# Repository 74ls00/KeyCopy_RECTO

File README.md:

### Простой копировщик домофонных ключей от RECTO.

#### Портативный одноплатный SMD вариант с батарейным питанием.
[Подробнее в Wiki](https://github.com/74ls00/KeyCopy_RECTO/wiki).

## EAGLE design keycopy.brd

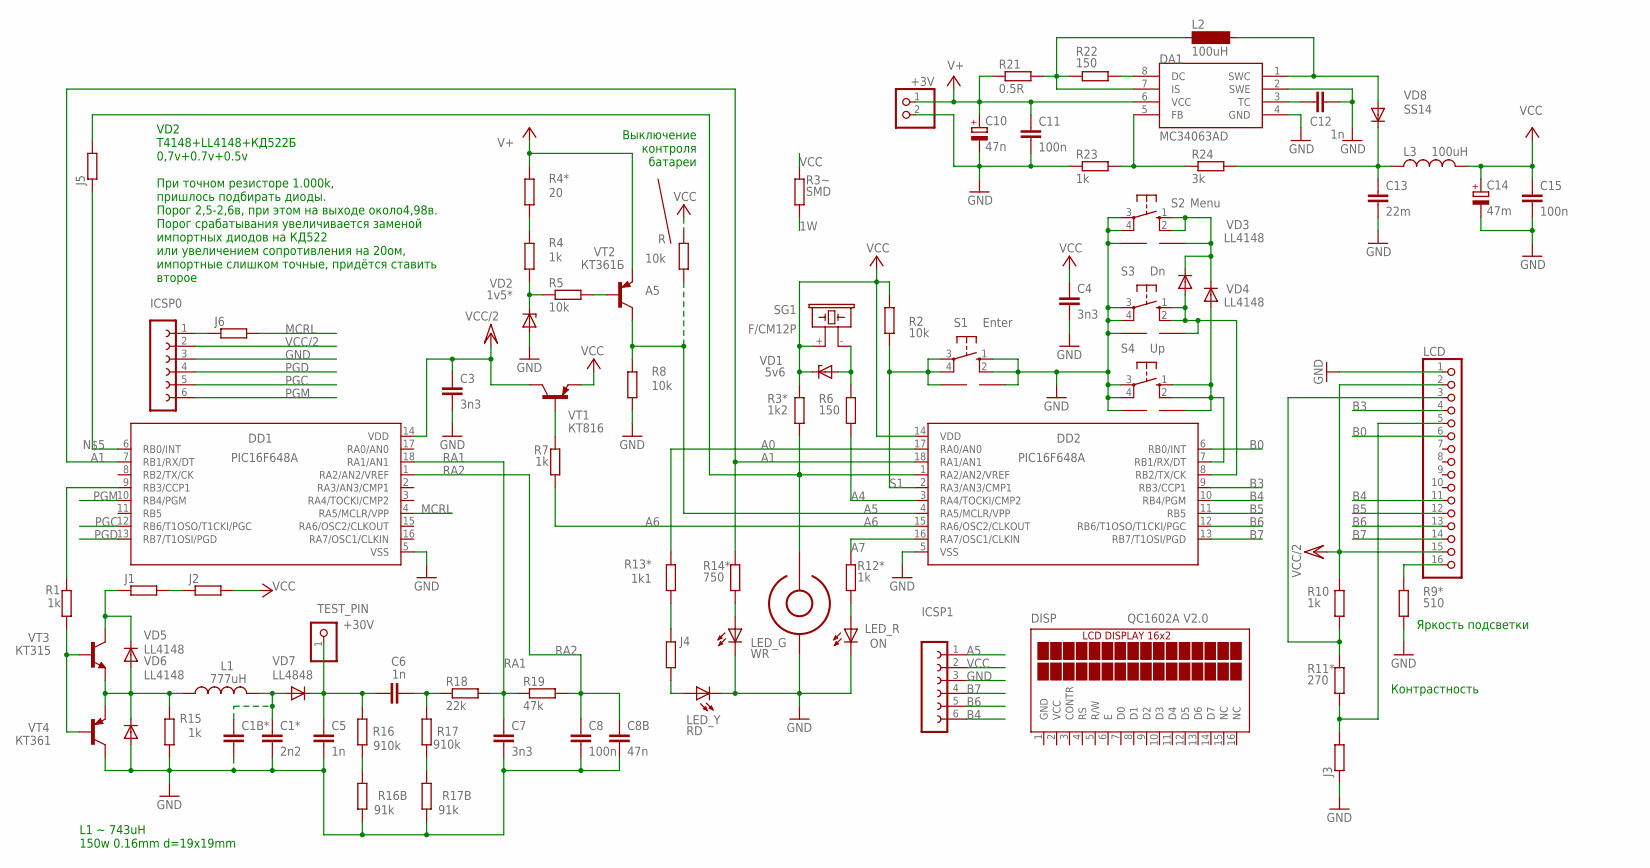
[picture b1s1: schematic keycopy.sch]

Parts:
+3V: PINHD-1X2; 1X02
C1*: 2n2; C025-030X050
C1B*: C-EU025-030X050; C025-030X050
C3, C4: 3n3; CAP-PTH-LARGE
C5, C6: 1n; C025-030X050
C7: 3n3; C025-030X050
C8: 100n; C025-030X050
C8B: 47n; C025-030X050
C10: 47n; E2,5-6
C11, C15: 100n; C0805K
C12: 1n; C0805K
C13: 22m; C1210
C14: 47m; E2,5-6
DA1: MC34063AD; SOIC8
DD1: PIC16F648A; SO-18W; MPN PIC16F628-20I/SO
DD2: PIC16F648A; SO-18W
DISP: QC1602A V2.0; TUXGR_16X2_1
ICSP0, ICSP1: FE06-1; FE06
J1, J2, J3, J4, J5: R-EU_R1206W; R1206W
J6: R-EU_R0805W; R0805W
KEY: DS1990
L1: 777uH; 0207/2V
L2: 100uH; SD12K100
L3: 100uH; 0207/12
LCD: PINHD-1X16; 1X16
LED_G: WR; LED3MM
LED_R: ON; LED3MM
LED_Y: RD; LED3MM
R, R5: 10k; R0805
R1, R4: 1k; R1206W
R2, R8: 10k; R1206W
R3*: 1k2; 0204/7
R3~: SMD; M0805
R4*: 20; R0805
R6, R22: 150; R0805
R7, R10, R12*, R15, R23: 1k; R0805
R9*: 510; R0805
R11*: 270; 0207/10
R13*: 1k1; 0207/10
R14*: 750; 0207/10
R16, R17: 910k; R0805
R16B, R17B: 91k; R0805
R18: 22k; R0805
R19: 47k; R0805
R21: 0.5R; R0805
R24: 3k; R1206W
S1: Enter; B3F-10XX
S2: Menu; B3F-10XX
S3: Dn; B3F-10XX
S4: Up; B3F-10XX
SG1: F/CM12P
TEST_PIN: +30V; 1X01
U$1, U$6, U$7, U$8: PROGRAMMER_5.08; PROGRAMMER_KEY
VD1: 5v6; SOD80C
VD2: 1v5*; ZDIO-5
VD3, VD4, VD5, VD6: LL4148; SOD80C
VD7: LL4848; SOD80C
VD8: SS14; SMB
VT1: КТ816; TO126
VT2: КТ361Б; TO92-BCE
VT3: КТ315; TO92-ECB
VT4: КТ361; TO92-BCE

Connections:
1W: DD2.1 (RA2/AN2/VREF), J5.2, KEY.P$1, R3*.1, R3~.1
A0: DD2.17 (RA0/AN0), R13*.2
A1: DD1.7 (RB1/RX/DT), DD2.18 (RA1/AN1), R14*.2
A4: DD2.3 (RA4/TOCKI/CMP2), R6.1
A5: DD2.4 (RA5/MCLR/VPP), ICSP1.1, R.1, R8.2, VT2.C
A6: DD2.15 (RA6/OSC2/CLKOUT), R7.1
A7: DD2.16 (RA7/OSC1/CLKIN), R12*.2
B0: DD2.6 (RB0/INT), LCD.6
B3: DD2.9 (RB3/CCP1), LCD.4
B4: DD2.10 (RB4/PGM), ICSP1.6, LCD.11
B5: DD2.11 (RB5), LCD.12
B6: DD2.12 (RB6/T1OSO/T1CKI/PGC), ICSP1.5, LCD.13
B7: DD2.13 (RB7/T1OSI/PGD), ICSP1.4, LCD.14
GND: +3V.2, C1*.2, C1B*.2, C3.2, C4.2, C5.2, C7.2, C8.2, C8B.2, C10.-, C11.2, C12.2, C13.2, C14.-, C15.2, DA1.2 (SWE), DA1.4 (GND), DD1.5 (VSS), DD2.5 (VSS), DISP.1 (GND), ICSP0.3, ICSP1.3, J3.1, KEY.P$2, LCD.1, LED_G.K (C), LED_R.K (C), LED_Y.K (C), R8.1, R9*.1, R15.1, R16B.1, R17B.1, R23.1, S1.1 (S), S1.2 (S1), S2.3, S2.4 (P1), S3.3, S3.4 (P1), S4.3, S4.4 (P1), U$1.P$2, U$6.P$1, U$7.P$1, U$8.P$1, VD2.A, VD6.A, VT4.C
LG: LED_G.A, R14*.1
LR: LED_R.A, R12*.1
LY: J4.1, LED_Y.A
MCRL: DD1.4 (RA5/MCLR/VPP), J6.2
unnamed: R1.1, VT3.B, VT4.B
unnamed: C1*.1, C1B*.1, L1.2, VD7.A
unnamed: C13.1, L3.1, R24.2, VD8.C
unnamed: DD1.9 (RB3/CCP1), R1.2
unnamed: DD1.6 (RB0/INT), J5.1
unnamed: C5.1, C6.1, R16.2, TEST_PIN.1, VD7.C
unnamed: R7.2, VT1.3 (B)
unnamed: R6.2, SG1.- (2), VD1.A
unnamed: LCD.16, R9*.2
unnamed: J1.1, VD5.C, VT3.C
unnamed: R16.1, R16B.2
unnamed: LCD.3, R10.1, R11*.2
unnamed: DD2.7 (RB1/RX/DT), S4.1 (S), S4.2 (S1), U$6.P$2, VD4.A
unnamed: S2.1 (S), S2.2 (S1), U$8.P$2, VD3.C, VD4.C
unnamed: DD2.8 (RB2/TX/CK), S3.1 (S), S3.2 (S1), U$7.P$2, VD3.A
unnamed: C6.2, R17.2, R18.1
unnamed: R4.1, R5.1, VD2.C
unnamed: R5.2, VT2.B
unnamed: ICSP0.1, J6.1
unnamed: J4.2, R13*.1
unnamed: L1.1, R15.2, VD5.A, VD6.C, VT3.E, VT4.E
unnamed: J1.2, J2.1
unnamed: R17.1, R17B.2
unnamed: J3.2, LCD.5, R11*.1
unnamed: C12.1, DA1.3 (TC)
unnamed: DA1.1 (SWC), L2.2, VD8.A
unnamed: DA1.7 (IS), L2.1, R21.2, R22.1
unnamed: DA1.8 (DC), R22.2
unnamed: DA1.5 (FB), R23.2, R24.1
unnamed: R4.2, R4*.1
PGC: DD1.12 (RB6/T1OSO/T1CKI/PGC), ICSP0.5
PGD: DD1.13 (RB7/T1OSI/PGD), ICSP0.4
PGM: DD1.10 (RB4/PGM), ICSP0.6
RA1: C7.1, DD1.18 (RA1/AN1), R18.2, R19.1
RA2: C8.1, C8B.1, DD1.1 (RA2/AN2/VREF), R19.2
S1: DD2.2 (RA3/AN3/CMP1), R2.1, S1.3, S1.4 (P1), U$1.P$1
V+: +3V.1, C10.+, C11.1, DA1.6 (VCC), R4*.2, R21.1, VT2.E
VCC: C4.1, C14.+, C15.1, DD2.14 (VDD), DISP.2 (VCC), ICSP1.2, J2.2, L3.2, R.2, R2.2, R3*.2, R3~.2, SG1.+ (1), VD1.C, VT1.1 (E)
VCC/2: C3.1, DD1.14 (VDD), ICSP0.2, LCD.2, LCD.15, R10.2, VT1.2 (C)

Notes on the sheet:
Яркость подсветки
Контрастность
Выключение контроля батареи
L1 ~ 743uH 150w 0.16mm d=19x19mm
VD2 T4148+LL4148+КД522Б 0,7v+0.7v+0.5v При точном резисторе 1.000k, пришлось подбирать диоды. Порог 2,5-2,6в, при этом на выходе около4,98в. Порог срабатывания увеличивается заменой импортных диодов на КД522 или увеличением сопротивления на 20ом, импортные слишком точные, придётся ставить второе

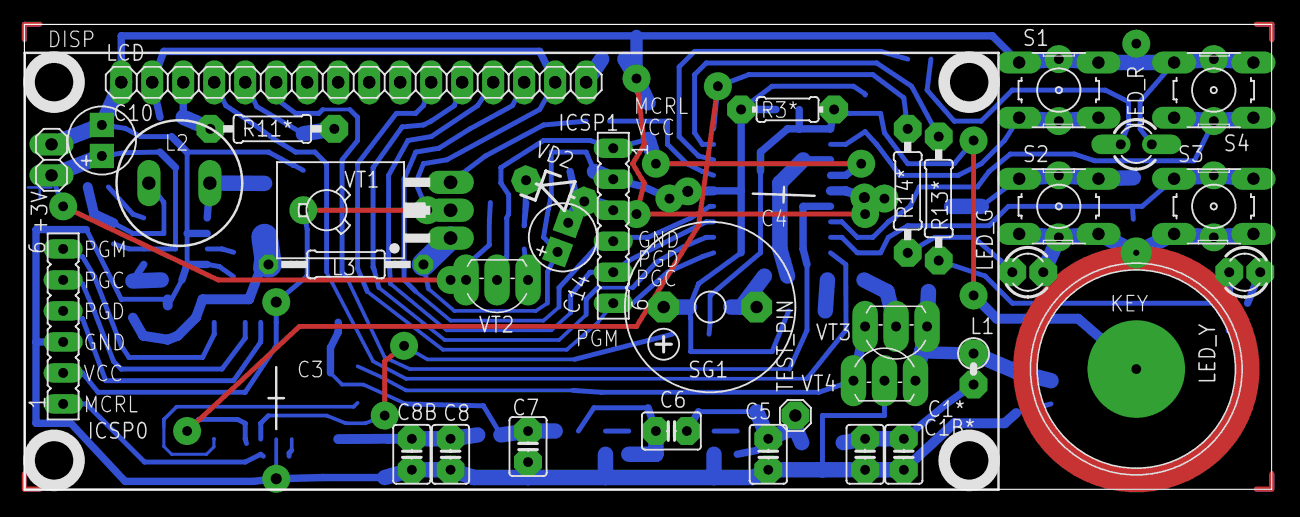
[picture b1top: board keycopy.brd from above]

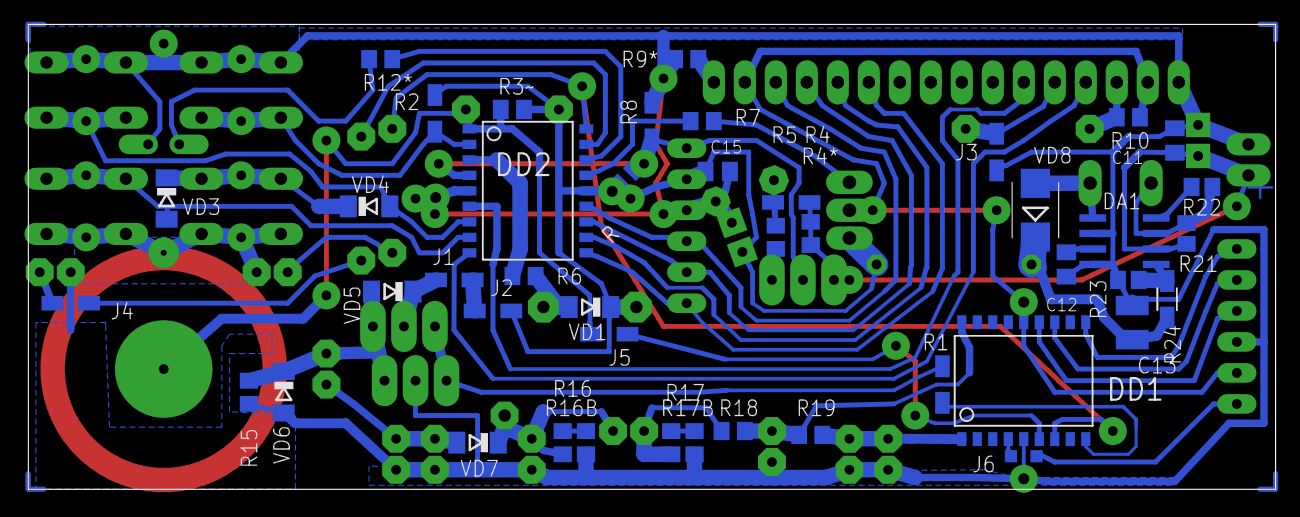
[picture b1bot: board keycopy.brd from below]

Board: 2 copper layers, 102.2 x 38.1 mm, 86 parts (44 on the bottom side), 57 nets.

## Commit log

2016-05-07 b001
2016-05-08 b002
2016-05-08 b003
2016-05-08 b004
2016-05-08 b005
2016-05-08 b006
2016-05-08 b007
2016-05-08 b008
2016-05-08 b010
2016-05-08 b011
2016-05-08 v0.1
2016-05-08 v0.2
2016-05-09 v0.21
2016-05-09 v0.22
2016-05-11 v0.3
2016-05-11 v0.31
2016-05-11 v0.32
2016-05-13 v0.33
2016-07-05 2016.07.05
